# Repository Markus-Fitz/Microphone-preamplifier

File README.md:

# Microphone-preamplifier
 Preamplifier for an electret microphone capsule.

# Description
 The circuit consists of two OpAmp-stages which together have around 24dB gain. The OpAmps chosen for this project are OP27-OpAmps for their DIP8-package and relatively high gain-bandwidth-product. The Coupling-capacitors are foil-capacitors, to minimizie their impact on the sonic performance. The Amplifier is designed to work off of a 12V power-supply, which is regulated down to 8V with an internal linear regulator. An optional gain-adjustment can be fitted to the second gain stage.

 # Specs
  The simulated Bode-plot of the amplifier shows a flat gain-curve (-1dB relative to 1kHz) from <10Hz to >200kHz.

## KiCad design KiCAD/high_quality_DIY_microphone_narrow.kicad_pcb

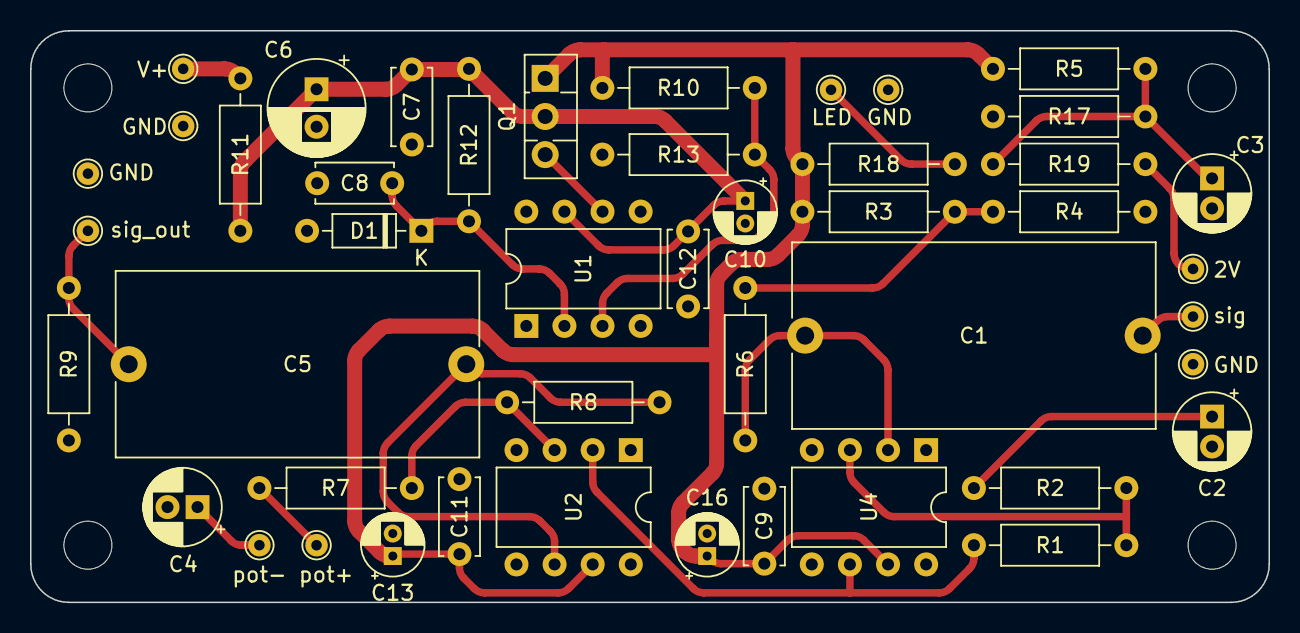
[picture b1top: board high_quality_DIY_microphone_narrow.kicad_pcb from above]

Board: 2 copper layers, 82.6 x 38.1 mm, 50 parts (0 on the bottom side), 21 nets.

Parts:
C1, C5: 3.3uF; C_Rect_L24.0mm_W12.2mm_P22.50mm_MKT
C2, C3, C4: 22uF; CP_Radial_D5.0mm_P2.00mm
C6: 100uF; CP_Radial_D6.3mm_P2.50mm
C7, C8, C9, C11, C12: 100nF; C_Disc_D5.0mm_W2.5mm_P5.00mm
C10, C13, C16: 10uF; CP_Radial_D4.0mm_P1.50mm
D1: 6.2V; D_DO-35_SOD27_P7.62mm_Horizontal
H1, H2, H3, H4: MountingHole; MountingHole_3.2mm_M3_DIN965
J1: sig_in; TestPoint_THTPad_D1.5mm_Drill0.7mm
J2: 12V; TestPoint_THTPad_D1.5mm_Drill0.7mm
J3: Pot_GND; TestPoint_THTPad_D1.5mm_Drill0.7mm
J4: sig_out; TestPoint_THTPad_D1.5mm_Drill0.7mm
J5: LED+; TestPoint_THTPad_D1.5mm_Drill0.7mm
J6: Pot+; TestPoint_THTPad_D1.5mm_Drill0.7mm
J7: 2V; TestPoint_THTPad_D1.5mm_Drill0.7mm
J8, J9, J10: GND; TestPoint_THTPad_D1.5mm_Drill0.7mm
J11: LED-; TestPoint_THTPad_D1.5mm_Drill0.7mm
Q1: BD139; TO-126-3_Vertical
R1, R6, R8, R9: 47k; R_Axial_DIN0207_L6.3mm_D2.5mm_P10.16mm_Horizontal
R2, R7: 3.3k; R_Axial_DIN0207_L6.3mm_D2.5mm_P10.16mm_Horizontal
R3, R4, R12: 4.7k; R_Axial_DIN0207_L6.3mm_D2.5mm_P10.16mm_Horizontal
R5: 3k; R_Axial_DIN0207_L6.3mm_D2.5mm_P10.16mm_Horizontal
R10: 1.8k; R_Axial_DIN0207_L6.3mm_D2.5mm_P10.16mm_Horizontal
R11: 50; R_Axial_DIN0207_L6.3mm_D2.5mm_P10.16mm_Horizontal
R13: 6.2k; R_Axial_DIN0207_L6.3mm_D2.5mm_P10.16mm_Horizontal
R17: 1k; R_Axial_DIN0207_L6.3mm_D2.5mm_P10.16mm_Horizontal
R18: R_LED; R_Axial_DIN0207_L6.3mm_D2.5mm_P10.16mm_Horizontal
R19: 15k; R_Axial_DIN0207_L6.3mm_D2.5mm_P10.16mm_Horizontal
U1, U2, U4: DIP-8_W7.62mm

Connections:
/2V: C3.1, R5.1, R17.2, R19.1
/8V: C9.1, C11.1, C13.1, C16.1, Q1.1 (E), R3.2, R5.2, R10.2, R18.2, U2.7 (V+), U4.7 (V+)
/12V: J2.1, R11.1
/12V_filtered: C6.1, C7.1, C10.1, C12.1, Q1.2 (C), R11.2, R12.2, U1.7 (V+)
/LED+: J5.1, R18.1
/signal_input: C1.1, J1.1
GND: C2.2, C3.2, C4.2, C6.2, C7.2, C8.2, C9.2, C10.2, C11.2, C12.2, C13.2, C16.2, D1.2 (A), J8.1, J9.1, J10.1, J11.1, R4.1, R9.1, R13.1, R17.1, U1.4 (V-), U2.4 (V-), U4.4 (V-)
unnamed: C2.1, R2.1
unnamed: C8.1, D1.1 (K), R12.1, U1.2 (-)
unnamed: C4.1, J3.1
unnamed: C5.2, J4.1, R9.2
unnamed: J6.1, R7.1
unnamed: J7.1, R19.2
unnamed: Q1.3 (B), U1.6 (out)
unnamed: R3.1, R4.2, R6.1
unnamed: R10.1, R13.2, U1.3 (+)
unnamed: R7.2, R8.1, U2.3 (+)
unnamed: R1.2, U2.2 (-), U4.6 (out)
unnamed: C5.1, R8.2, U2.6 (out)
unnamed: R1.1, R2.2, U4.3 (+)
unnamed: C1.2, R6.2, U4.2 (-)

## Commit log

2024-04-08 Initial Commit.
    Initial Commit.
2024-04-08 Update README.md
    Extended Readme to include a description of the circuit and its basic specs.
2024-04-08 Cleanup
    Cleanup of KiCAD-folder.
